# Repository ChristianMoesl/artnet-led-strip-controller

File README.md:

# ArtNet LED-Strip Controller
This is a small LED controller for WS2815B leds, which can be accessed and controlled through the ArtNet protocol over Ethernet.

## Assembled PCB

##  LICENSE
The contents of this repository are covered under the [MIT License](./LICENSE).

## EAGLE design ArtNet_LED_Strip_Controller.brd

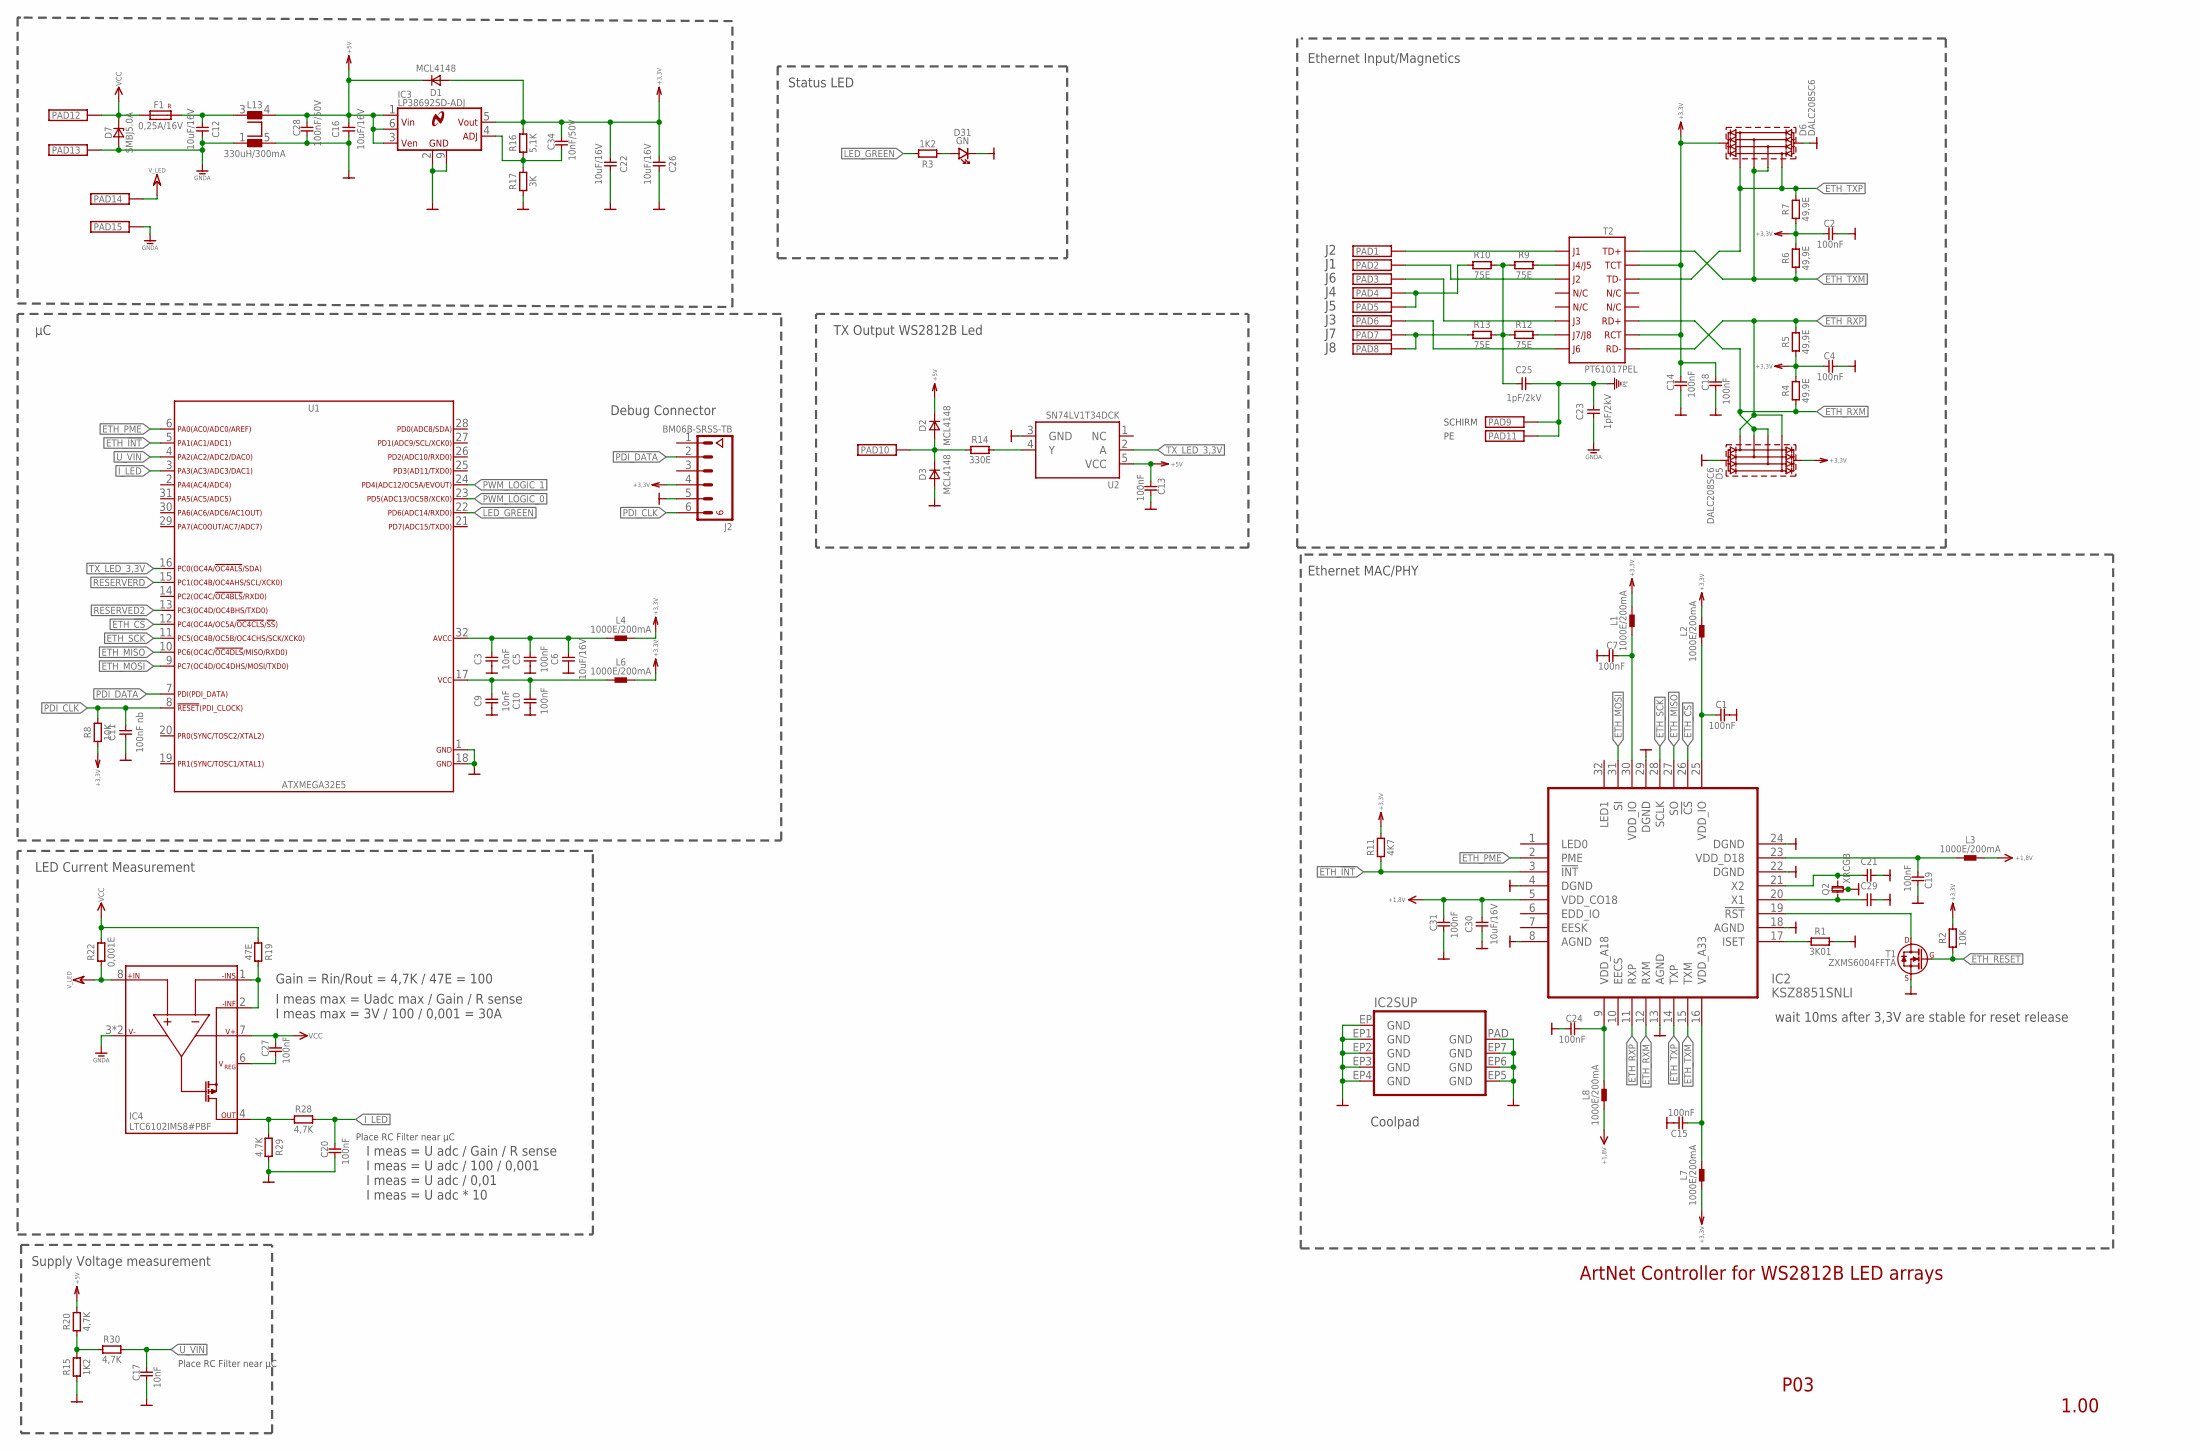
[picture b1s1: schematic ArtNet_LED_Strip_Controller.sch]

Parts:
C1, C2, C4, C5, C7, C10, C13, C14, C15, C18, C19, C20, C24, C27, C31: 100nF; 0603@1
C3, C9, C17: 10nF; 0603@1
C6, C12, C16, C22, C26, C30: 10uF/16V; 0805
C11: 100nF nb; 0603@1
C21, C29: C-0603; 0603@1
C23, C25: 1pF/2kV; 1206@1
C28: 100nF/50V; 0603@1
C34: 10nF/50V; 0603@1
D1, D2, D3: MCL4148; MICROMELF
D5, D6: DALC208SC6; SOT23-6L
D7: SMBJ5.0A; DO-214AA
D31: GN; 0603
F1: 0,25A/16V; 1206L
IC2: KSZ8851SNLI; QFN32_5X5
IC3: LP38692SD-ADJ; LLP-6
IC4: LTC6102IMS8#PBF; MS8
J2: BM06B-SRSS-TB
L1, L2, L3, L4, L6, L7, L8: 1000E/200mA; 0603
L13: 330uH/300mA; WE-SL1
PAD1, PAD2, PAD3, PAD4, PAD5, PAD6, PAD7, PAD8, PAD9, PAD10, PAD11: PADS-2X1.5; PAD_2MMX1,4MM
PAD12, PAD13, PAD14, PAD15: PADS-8X5_O_P; PAD_8MMX5MM_OHNE_PASTE
Q2: XRCGB
R1: 3K01; 0603
R2, R8: 10K; 0603
R3, R15: 1K2; 0603
R4, R5, R6, R7: 49,9E; 0603
R9, R10, R12, R13: 75E; 0603
R11: 4K7; 0603
R14: 330E; 0603
R16: 5,1K; 0603
R17: 3K; 0603
R19: 47E; 0603
R20, R28, R29, R30: 4,7K; 0603
R22: 0,001E; WSL2512_2
T1: ZXMS6004FFTA; SOT-23
T2: PT61017PEL; PT61017
U1: ATXMEGA32E5; 32_UQFN
U2: SN74LV1T34DCK; DCK0005A_N

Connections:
+1,8V: C30.2, C31.2, IC2.5 (VDD_CO18), L3.2, L8.1
+3,3V: C2.1, C4.1, C14.2, C18.2, C22.1, C26.1, C34.2, D1.A, D5.2 (REF2), D6.2 (REF2), IC3.5 (VOUT), J2.4, L1.2, L2.2, L4.2, L6.2, L7.1, R2.2, R4.2, R5.1, R6.2, R7.1, R8.1, R11.2, R16.2, T2.2, T2.7
+5V: C13.1, C16.2, C28.2, D1.K, D2.K, IC3.1 (VIN), IC3.3 (VEN), IC3.6 (VIN1), L13.4 (3), R20.2, U2.5 (VCC)
ETH_!CS: IC2.26 (!CS), U1.12 (PC4)
ETH_!INT: IC2.3 (!INT), R11.1, U1.5 (PA1)
ETH_MISO: IC2.27 (SO), U1.10 (PC6)
ETH_MOSI: IC2.31 (SI), U1.9 (PC7)
ETH_PME: IC2.2 (PME), U1.6 (PA0)
ETH_RESET: R2.1, T1.1 (G)
ETH_RXM: D5.3 (I/O2), D5.4 (I/O3), IC2.12 (RXM), R4.1, T2.6
ETH_RXP: D5.1 (I/O1), D5.6 (I/O4), IC2.11 (RXP), R5.2, T2.8
ETH_SCK: IC2.28 (SCLK), U1.11 (PC5)
ETH_TXM: D6.3 (I/O2), D6.4 (I/O3), IC2.15 (TXM), R6.1, T2.1
ETH_TXP: D6.1 (I/O1), D6.6 (I/O4), IC2.14 (TXP), R7.2, T2.3
GND: C1.2, C2.2, C3.1, C4.2, C5.1, C6.1, C7.2, C9.1, C10.1, C11.1, C13.2, C14.1, C15.2, C16.1, C17.1, C18.1, C19.2, C20.1, C21.2, C22.2, C24.1, C26.2, C28.1, C29.2, C30.1, C31.1, D3.A, D5.5 (REF1), D6.5 (REF1), D31.K, IC2.4 (DGND), IC2.8 (AGND), IC2.13 (AGND), IC2.18 (AGND), IC2.22 (DGND), IC2.24 (DGND), IC2.29 (DGND), IC2.EP (GND), IC2.EP1 (GND), IC2.EP2 (GND), IC2.EP3 (GND), IC2.EP4 (GND), IC2.EP5 (GND), IC2.EP6 (GND), IC2.EP7 (GND), IC2.PAD (GND), IC3.2 (GND), IC3.9 (GND1), J2.5, L13.5 (2), Q2.3, Q2.4, R1.2, R15.1, R17.1, R29.2, T1.2 (S), U1.1 (GND), U1.18 (GND), U2.3 (GND)
GNDA: C12.2, C23.1, D7.A, IC4.3 (V-), IC4.5 (V-), L13.1, PAD13.P$1, PAD15.P$1
I_LED: C20.2, R28.2, U1.3 (PA3)
LED_GREEN: R3.2, U1.22 (PD6)
unnamed: IC2.17 (ISET), R1.1
unnamed: C9.2, C10.2, L6.1, U1.17 (VCC)
unnamed: IC2.19 (!RST), T1.3 (D)
unnamed: C7.1, IC2.30 (VDD_IO), L1.1
unnamed: C1.1, IC2.25 (VDD_IO), L2.1
unnamed: C3.2, C5.2, C6.2, L4.1, U1.32 (AVCC)
unnamed: D2.A, D3.K, PAD10.1, R14.1
unnamed: C27.1, IC4.6 (VREG)
unnamed: C34.1, IC3.4 (ADJ), R16.1, R17.2
unnamed: C25.1, R9.1, R10.2, R12.1, R13.2
unnamed: R12.2, T2.10
unnamed: C29.1, IC2.20 (X1), Q2.1
unnamed: C12.1, F1.2, L13.3 (4)
unnamed: R9.2, T2.15
unnamed: PAD2.1, T2.14
unnamed: IC4.4 (OUT), R28.1, R29.1
unnamed: PAD4.1, PAD5.1, R10.1
unnamed: C15.1, IC2.16 (VDD_A33), L7.2
unnamed: PAD1.1, T2.16
unnamed: PAD3.1, T2.11
unnamed: C21.1, IC2.21 (X2), Q2.2
unnamed: PAD7.1, PAD8.1, R13.1
unnamed: R15.2, R20.1, R30.1
unnamed: C24.2, IC2.9 (VDD_A18), L8.2
unnamed: PAD6.1, T2.9
unnamed: R14.2, U2.4 (Y)
unnamed: IC4.1 (-INS), IC4.2 (-INF), R19.2
unnamed: D31.A, R3.1
PDI_CLK: C11.2, J2.6, R8.2, U1.8 (PDI-CLK/!RESET)
PDI_DATA: J2.2, U1.7 (PDI-DATA)
PE: C23.2, C25.2, PAD9.1, PAD11.1
PWM_LOGIC_0: U1.23 (PD5)
PWM_LOGIC_1: U1.24 (PD4)
RESERVED2: U1.13 (PC3)
RESERVERD: U1.15 (PC1)
TX_LED_3,3V: U1.16 (PC0), U2.2 (A)
U_VIN: C17.2, R30.2, U1.4 (PA2)
VCC: C27.2, D7.K, F1.1, IC4.7 (V+), PAD12.P$1, R19.1, R22.2
VDD_D18: C19.1, IC2.23 (VDD_D18), L3.1
V_LED: IC4.8 (+IN), PAD14.P$1, R22.1

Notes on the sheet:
Place RC Filter near µC
wait 10ms after 3,3V are stable for reset release
SCHIRM
Gain = Rin/Rout = 4,7K / 47E = 100
I meas max = Uadc max / Gain / R sense I meas max = 3V / 100 / 0,001 = 30A
I meas = U adc / Gain / R sense I meas = U adc / 100 / 0,001 I meas = U adc / 0,01 I meas = U adc * 10
LED Current Measurement
Ethernet Input/Magnetics
Supply Voltage measurement
Debug Connector
Coolpad
TX Output WS2812B Led
Ethernet MAC/PHY
Status LED
P03
1.00
ArtNet Controller for WS2812B LED arrays

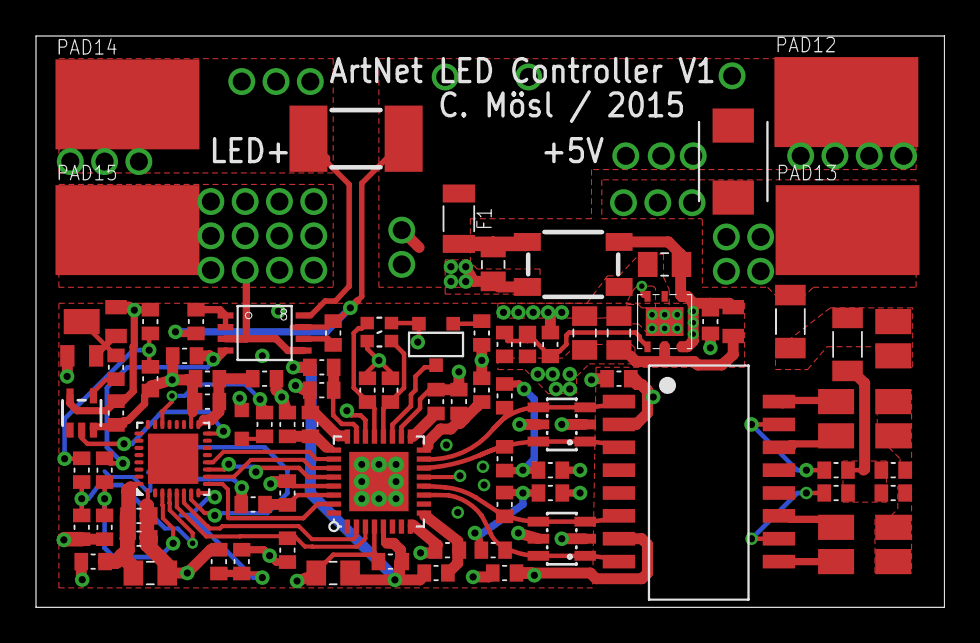
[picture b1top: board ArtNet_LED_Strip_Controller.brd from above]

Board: 4 copper layers, 50.5 x 31.7 mm, 94 parts (1 on the bottom side), 54 nets.

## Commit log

2016-10-19 Added license information and documentation
2016-10-19 Fixed format
